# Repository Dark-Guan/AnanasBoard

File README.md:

# AnanasBoard
AnanasBoard is Designed for Stepper Closeloop Control.

<br />本作品采用<a rel="license" href="http://creativecommons.org/licenses/by/4.0/">知识共享署名 4.0 国际许可协议</a>进行许可。

如果你认为我做的这些对你来说是有价值的, 并鼓励我进行更多开源和免费的开发. 那你可以资助我, 就算是一杯咖啡...

If you find my work useful and you want to encourage the development of more free resources, you can do it by donating...

##feature

1. AMS5600 and Quadrature Encoder Supported  
2. Intelligent Tuning of the Motor Current  
3. Up to 30Khz Pulse Input Supported  
4. Up to 60Khz Stepper Driver PWM with Trapezoid Acceleration  
5. Internal PID Speed Controller  

##driver
1. A4988 and Drv8825 supported.
2. PWM DA function supported.With the  Tale:
    *PWM frequence needs to be up to 10Khz*

| IC| divider resistance | Capacitance | 5V| 3.3V
| ---------------- | ---------------- | ---------------- | ---------------- | ---------------- 
| A4988 | 10KOhm | 0.1uf | 4.7KOhm | 10KOhm
| drv8825 | 10KOhm | 0.1uf | 2.7KOhm | 3.3KOhm

circuit: voltage division circuit with a Capacitance(0.1uf)  
More Info : _[A4988](http://www.allegromicro.com/~/media/Files/Datasheets/A4988-Datasheet.ashx?la=zh-CN) and [Drv8825](http://www.ti.com/lit/ds/symlink/drv8825.pdf)datasheet_.  

# Eagle

Eagle 7.2 Used

# SoftWare
https://git.oschina.net/GaryPillow/Ananas
## back up
https://github.com/Dark-Guan/Ananas

https://github.com/Dark-Guan/Ananas/tree/master/binary

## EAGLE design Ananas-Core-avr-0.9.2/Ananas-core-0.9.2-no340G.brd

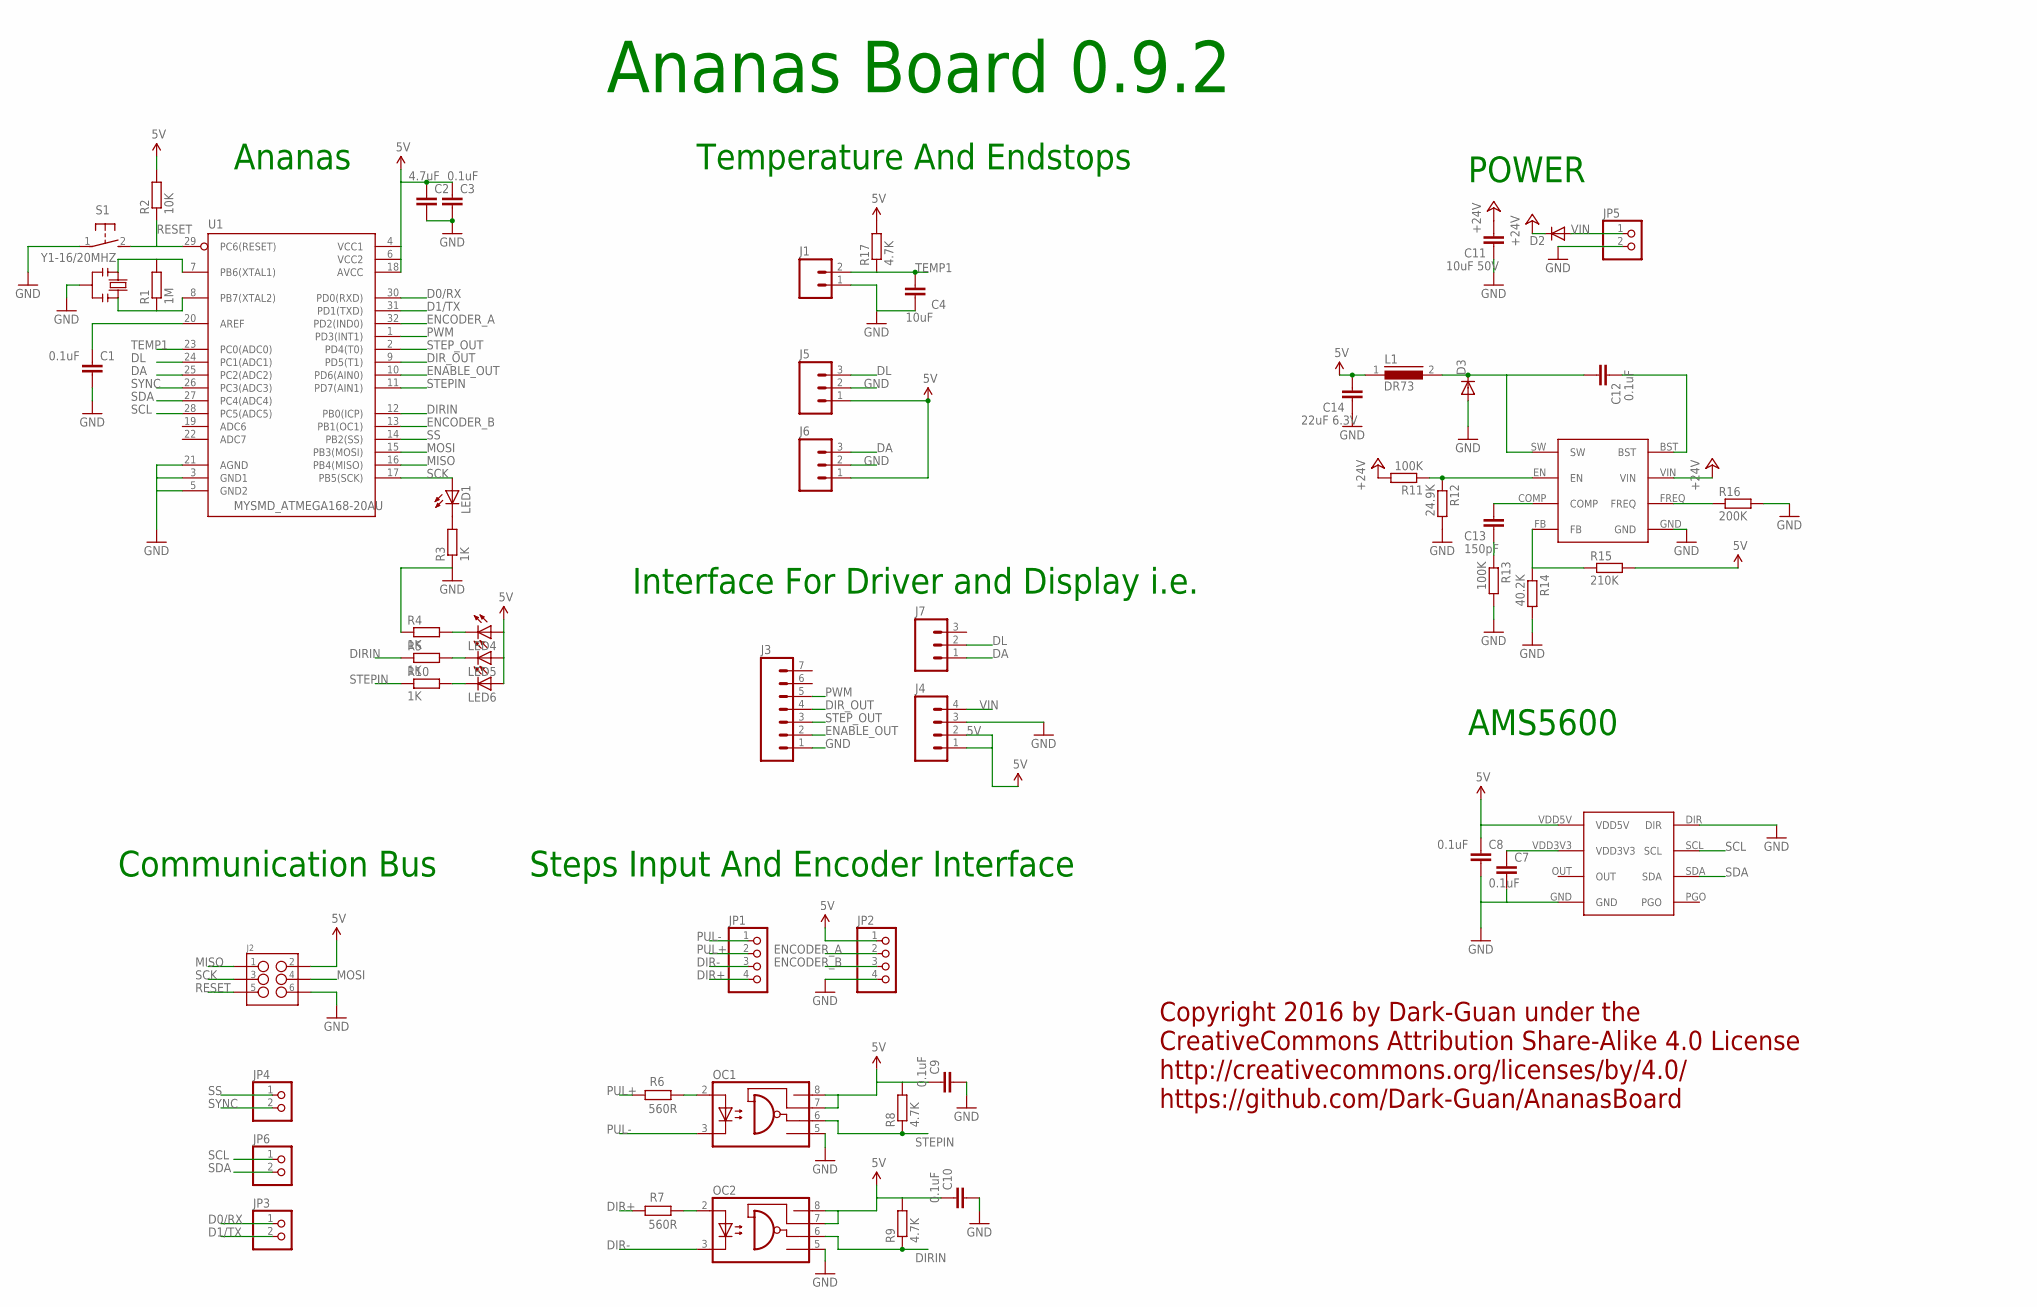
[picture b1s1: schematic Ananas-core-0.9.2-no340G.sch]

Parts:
C1, C3, C7, C8, C9, C10, C12: 0.1uF; C0603K
C2: 4.7uF; C0603K
C4: 10uF; C0603K
C11: 10uF 50V; C0805
C13: 150pF; C0603K
C14: 22uF 6.3V; C0805
D2, D3: DIODE_DIODE-SMB; DIODE_SMB
J1: M02PTH; 1X02
J2: M03X2NO_SILK; 2X3-NS
J3: M07; 1X07
J4: M04PTH; 1X04
J5, J6, J7: M03PTH; 1X03
JP1, JP2: PINHD-1X4/OCT; 1X04/OCT
JP3, JP4, JP5, JP6: PINHD-1X2/OCT; 1X02/OCT
L1: DR73
LED1, LED4, LED5, LED6: LEDCHIPLED_0603; CHIPLED_0603
MP1854: MP1584
OC1, OC2: OPTOCOUPLER_(2)_HCPL0600; OPTOCOUPLER_(2)_SOIC08
R1: 1M; R0603
R2: 10K; R0603
R3, R4, R5, R10: 1K; R0603
R6, R7: 560R; R0603
R8, R9, R17: 4.7K; R0603
R11, R13: 100K; R0603
R12: 24.9K; R0603
R14: 40.2K; R0603
R15: 210K; R0603
R16: 200K; R0603
S1: 31-XX; B3F-31XX
U1: MYSMD_ATMEGA168-20AU; MYSMD_QFP032
U$1: ARDUINO_AS5600
Y1-16/20MHZ: MYSMD2_RESONATORMU; MYSMD2_RESONATOR

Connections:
5V: C2.1, C3.1, C8.1, C9.1, C10.1, C14.2, J2.2, J4.1, J4.2, J5.1, J6.1, JP2.1, L1.1, LED4.A, LED5.A, LED6.A, OC1.7 (VE), OC1.8 (VCC), OC2.7 (VE), OC2.8 (VCC), R2.2, R8.2, R9.2, R15.2, R17.2, U1.4 (VCC1), U1.6 (VCC2), U1.18 (AVCC), U$1.VDD5V
+24V: C11.2, D2.C, MP1854.VIN, R11.2
D0/RX: JP3.1, U1.30 (PD0(RXD))
D1/TX: JP3.2, U1.31 (PD1(TXD))
DA: J6.3, J7.1, U1.25 (PC2(ADC2))
DIR+: JP1.4, R7.2
DIR-: JP1.3, OC2.3 (C)
DIRIN: OC2.6 (VO), R5.1, R9.1, U1.12 (PB0(ICP))
DIR_OUT: J3.4, U1.9 (PD5(T1))
DL: J5.3, J7.2, U1.24 (PC1(ADC1))
ENABLE_OUT: J3.2, U1.10 (PD6(AIN0))
ENCODER_A: JP2.2, U1.32 (PD2(IND0))
ENCODER_B: JP2.3, U1.13 (PB1(OC1))
GND: C1.2, C2.2, C3.2, C4.1, C7.2, C8.2, C9.2, C10.2, C11.1, C14.1, D3.A, J1.1, J2.6, J3.1, J4.3, J5.2, J6.2, JP2.4, JP5.2, MP1854.GND, OC1.5 (GND), OC2.5 (GND), R3.1, R4.1, R12.2, R13.2, R14.2, R16.2, S1.1, U1.3 (GND1), U1.5 (GND2), U1.21 (AGND), U$1.DIR, U$1.GND, Y1-16/20MHZ.2
MISO: J2.1, U1.16 (PB4(MISO))
MOSI: J2.4, U1.15 (PB3(MOSI))
unnamed: R1.2, U1.7 (PB6(XTAL1)), Y1-16/20MHZ.1
unnamed: R1.1, U1.8 (PB7(XTAL2)), Y1-16/20MHZ.3
unnamed: C1.1, U1.20 (AREF)
unnamed: OC1.2 (A), R6.1
unnamed: LED1.C, R3.2
unnamed: OC2.2 (A), R7.1
unnamed: C13.1, R13.1
unnamed: C7.1, U$1.VDD3V3
unnamed: MP1854.FREQ, R16.1
unnamed: C12.1, MP1854.BST
unnamed: C12.2, D3.C, L1.2, MP1854.SW
unnamed: MP1854.EN, R11.1, R12.1
unnamed: C13.2, MP1854.COMP
unnamed: MP1854.FB, R14.1, R15.1
unnamed: LED4.C, R4.2
unnamed: LED5.C, R5.2
unnamed: LED6.C, R10.2
PUL+: JP1.2, R6.2
PUL-: JP1.1, OC1.3 (C)
PWM: J3.5, U1.1 (PD3(INT1))
RESET: J2.5, R2.1, S1.2 (S), U1.29 (PC6(RESET))
SCK: J2.3, LED1.A, U1.17 (PB5(SCK))
SCL: JP6.1, U1.28 (PC5(ADC5)), U$1.SCL
SDA: JP6.2, U1.27 (PC4(ADC4)), U$1.SDA
SS: JP4.1, U1.14 (PB2(SS))
STEPIN: OC1.6 (VO), R8.1, R10.1, U1.11 (PD7(AIN1))
STEP_OUT: J3.3, U1.2 (PD4(T0))
SYNC: JP4.2, U1.26 (PC3(ADC3))
TEMP1: C4.2, J1.2, R17.1, U1.23 (PC0(ADC0))
VIN: D2.A, J4.4, JP5.1

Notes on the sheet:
Communication Bus
Steps Input And Encoder Interface
AMS5600
Interface For Driver and Display i.e.
Temperature And Endstops
POWER
Copyright 2016 by Dark-Guan under the CreativeCommons Attribution Share-Alike 4.0 License http://creativecommons.org/licenses/by/4.0/ https://github.com/Dark-Guan/AnanasBoard
Ananas Board 0.9.2
Ananas

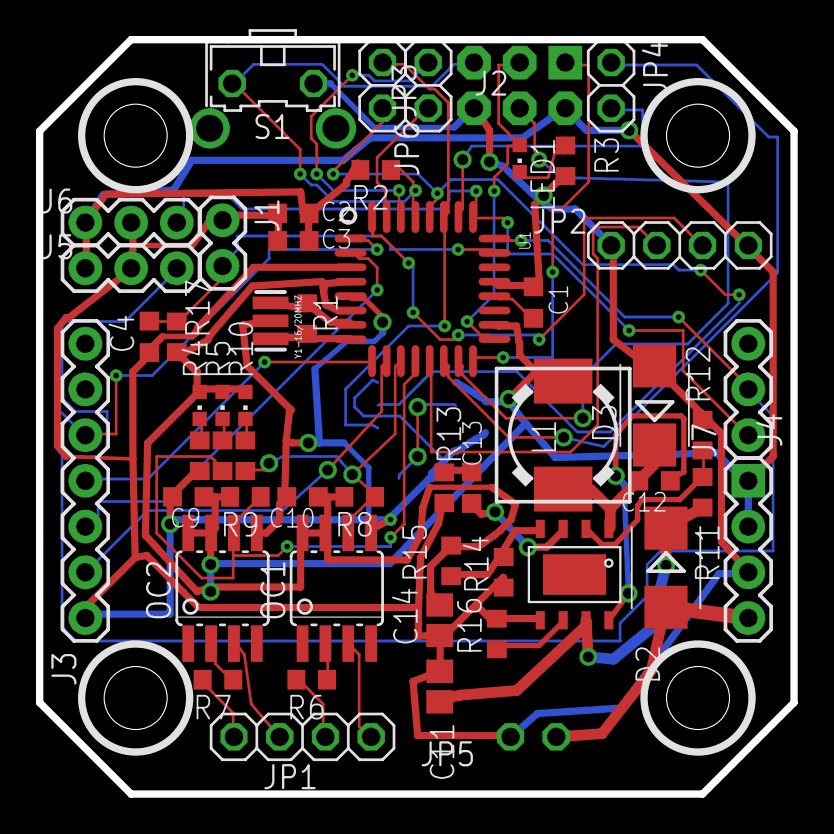
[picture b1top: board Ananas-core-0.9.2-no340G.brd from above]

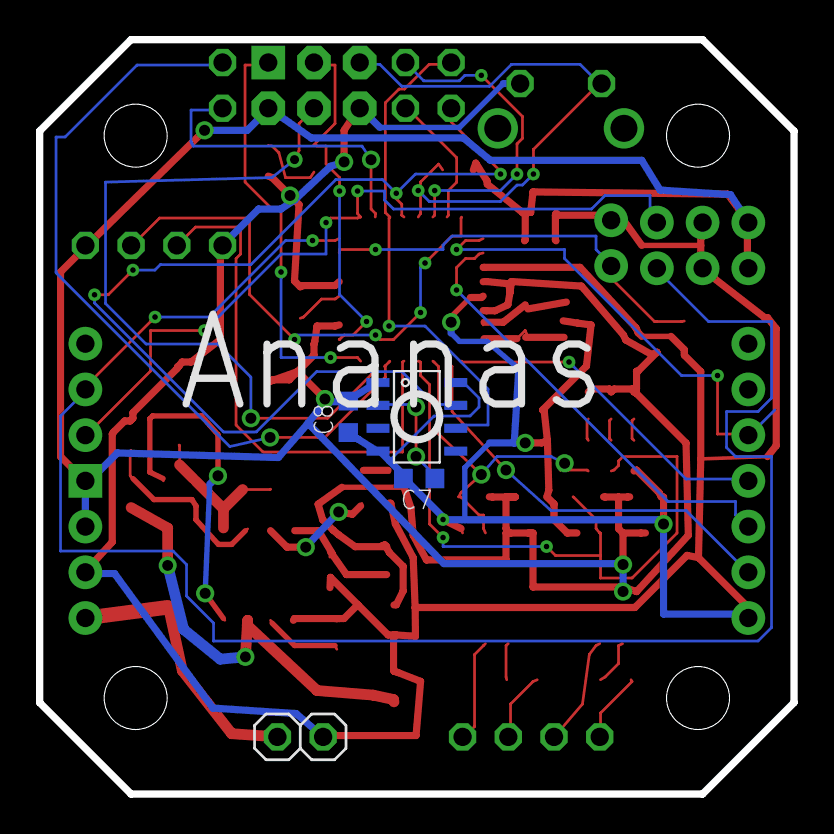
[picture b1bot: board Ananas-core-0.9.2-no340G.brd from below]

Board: 2 copper layers, 41.9 x 41.9 mm, 56 parts (4 on the bottom side), 46 nets.

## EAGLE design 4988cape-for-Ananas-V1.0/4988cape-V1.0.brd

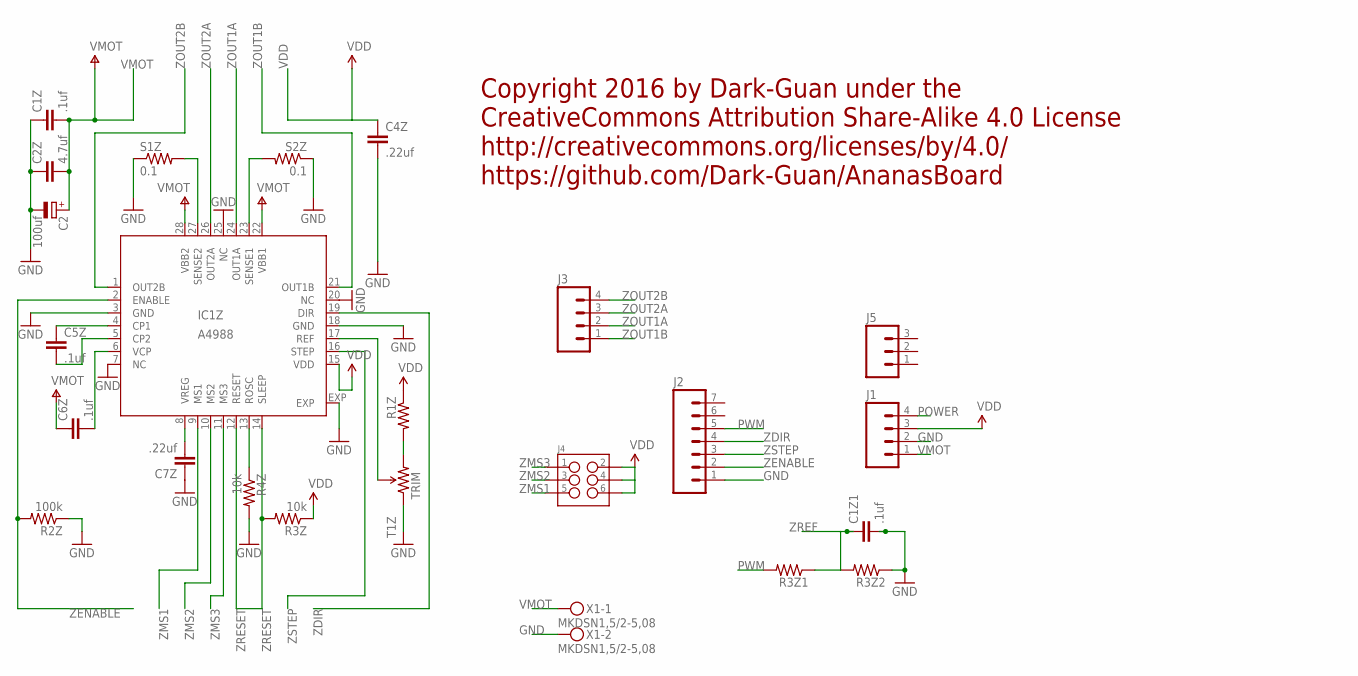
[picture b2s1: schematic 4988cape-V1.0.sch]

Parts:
C1Z, C1Z1, C5Z, C6Z: .1uf; 0402-CAP
C2: 100uf; 153CLV-0605
C2Z: 4.7uf; 0402-CAP
C4Z, C7Z: .22uf; 0402-CAP
IC1Z: A4988; QFN28ET
J1, J3: M04PTH; 1X04
J2: M07; 1X07
J4: M03X2NO_SILK; 2X3-NS
J5: M03PTH; 1X03
R1Z, R3Z1, R3Z2: RESISTOR0402-RES; 0402-RES
R2Z: 100k; 0402-RES
R3Z, R4Z: 10k; 0402-RES
S1Z, S2Z: 0.1; 0805
T1Z: TRIM; TRIMPOT-3MM
X1: MKDSN1,5/2-5,08

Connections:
GND: C1Z.1, C1Z1.2, C2.-, C2Z.1, C4Z.2, C7Z.1, IC1Z.3 (GND), IC1Z.7 (NC), IC1Z.18 (GND), IC1Z.20 (NC), IC1Z.25 (NC), IC1Z.EXP, J1.2, J2.1, R2Z.1, R3Z2.1, R4Z.2, S1Z.1, S2Z.1, T1Z.1 (CCW), X1.2
POWER: J1.4
PWM: J2.5, R3Z1.2
VDD: C4Z.1, IC1Z.15 (VDD), J1.3, J4.2, J4.4, J4.6, R1Z.1, R3Z.1
VMOT: C1Z.2, C2.+, C2Z.2, C6Z.1, IC1Z.22 (VBB1), IC1Z.28 (VBB2), J1.1, X1.1
ZCP1: C5Z.1, IC1Z.4 (CP1)
ZCP2: C5Z.2, IC1Z.5 (CP2)
ZDIR: IC1Z.19 (DIR), J2.4
ZENABLE: IC1Z.2 (ENABLE), J2.2, R2Z.2
ZMS1: IC1Z.9 (MS1), J4.5
ZMS2: IC1Z.10 (MS2), J4.3
ZMS3: IC1Z.11 (MS3), J4.1
ZOUT1A: IC1Z.24 (OUT1A), J3.2
ZOUT1B: IC1Z.21 (OUT1B), J3.1
ZOUT2A: IC1Z.26 (OUT2A), J3.3
ZOUT2B: IC1Z.1 (OUT2B), J3.4
ZREF: C1Z1.1, IC1Z.17 (REF), R3Z1.1, R3Z2.2, T1Z.2 (WIPER)
ZREF2: R1Z.2, T1Z.3 (CW)
ZRESET: IC1Z.12 (RESET), IC1Z.14 (SLEEP), R3Z.2
ZROSC: IC1Z.13 (ROSC), R4Z.1
ZSENSE1: IC1Z.23 (SENSE1), S2Z.2
ZSENSE2: IC1Z.27 (SENSE2), S1Z.2
ZSTEP: IC1Z.16 (STEP), J2.3
ZVCP: C6Z.2, IC1Z.6 (VCP)
ZVREG: C7Z.2, IC1Z.8 (VREG)

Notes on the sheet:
Copyright 2016 by Dark-Guan under the CreativeCommons Attribution Share-Alike 4.0 License http://creativecommons.org/licenses/by/4.0/ https://github.com/Dark-Guan/AnanasBoard

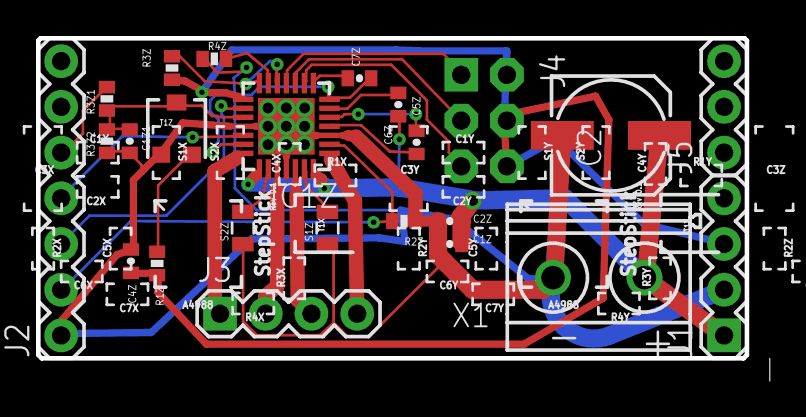
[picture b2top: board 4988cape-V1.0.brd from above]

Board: 2 copper layers, 40.5 x 18.9 mm, 24 parts (0 on the bottom side), 24 nets.

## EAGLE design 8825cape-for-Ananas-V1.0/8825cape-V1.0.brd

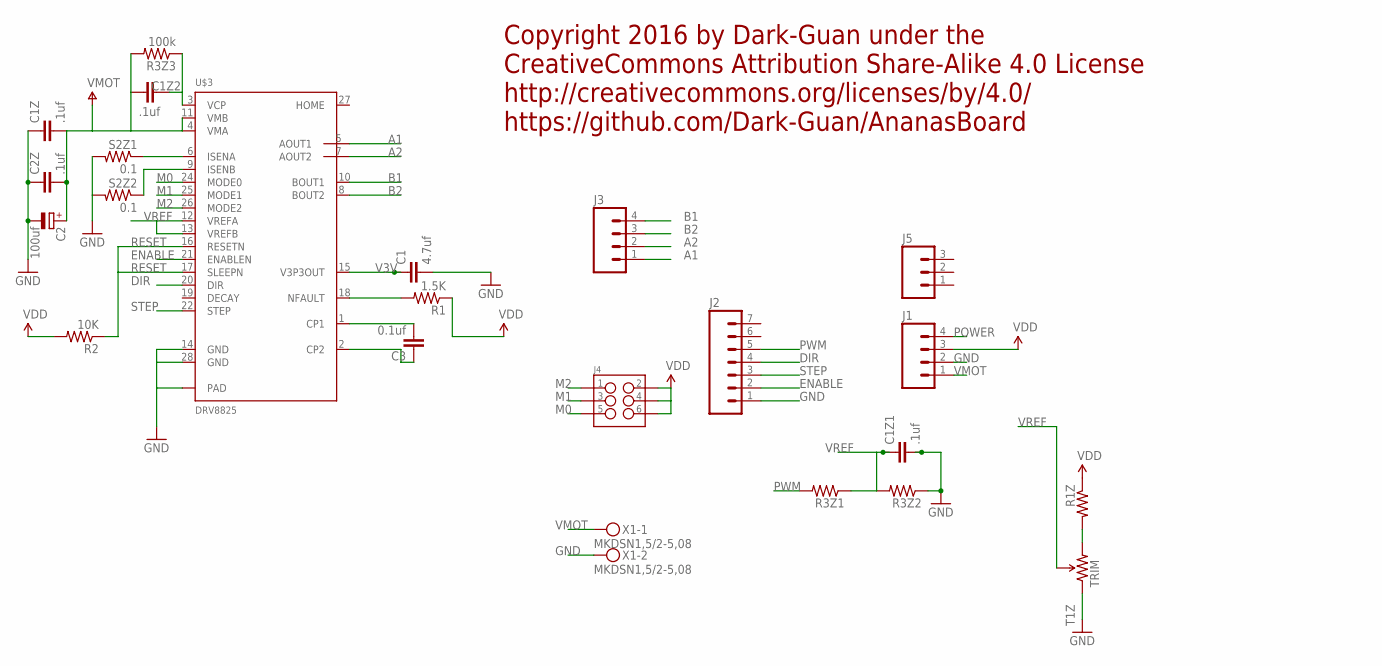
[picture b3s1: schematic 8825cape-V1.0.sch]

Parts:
C1: 4.7uf; 0402-CAP
C1Z, C1Z1, C1Z2, C2Z: .1uf; 0402-CAP
C2: 100uf; 153CLV-0605
C3: 0.1uf; 0402-CAP
J1, J3: M04PTH; 1X04
J2: M07; 1X07
J4: M03X2NO_SILK; 2X3-NS
J5: M03PTH; 1X03
R1: 1.5K; 0402-RES
R1Z, R3Z1, R3Z2: RESISTOR0402-RES; 0402-RES
R2: 10K; 0402-RES
R3Z3: 100k; 0402-RES
S2Z1, S2Z2: 0.1; 0805
T1Z: TRIM; TRIMPOT-3MM
U$3: DRV8825; HTSSOP28
X1: MKDSN1,5/2-5,08

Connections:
A1: J3.1, U$3.5 (AOUT1)
A2: J3.2, U$3.7 (AOUT2)
B1: J3.4, U$3.10 (BOUT1)
B2: J3.3, U$3.8 (BOUT2)
DIR: J2.4, U$3.20 (DIR)
ENABLE: J2.2, U$3.21 (ENABLEN)
GND: C1.2, C1Z.1, C1Z1.2, C2.-, C2Z.1, J1.2, J2.1, R3Z2.1, S2Z1.2, S2Z2.2, T1Z.1 (CCW), U$3.14 (GND), U$3.28 (GND), U$3.GND@10 (PAD), U$3.GND@11 (PAD), U$3.GND@12 (PAD), U$3.GND@13 (PAD), U$3.GND@14 (PAD), U$3.GND@15 (PAD), U$3.GND@16 (PAD), U$3.GND@17 (PAD), U$3.GND@18 (PAD), U$3.GND@19 (PAD), U$3.GND@20 (PAD), U$3.GND@21 (PAD), U$3.GND@22 (PAD), U$3.GND@23 (PAD), U$3.GND@24 (PAD), U$3.GND@25 (PAD), U$3.GND@26 (PAD), U$3.GND@27 (PAD), U$3.GND@28 (PAD), U$3.GND@29 (PAD), U$3.GND@30 (PAD), U$3.GND@PAD (PAD), X1.2
M0: J4.5, U$3.24 (MODE0)
M1: J4.3, U$3.25 (MODE1)
M2: J4.1, U$3.26 (MODE2)
unnamed: S2Z1.1, U$3.6 (ISENA)
unnamed: C1Z2.1, R3Z3.1, U$3.3 (VCP)
unnamed: C3.2, U$3.1 (CP1)
unnamed: S2Z2.1, U$3.9 (ISENB)
unnamed: C3.1, U$3.2 (CP2)
unnamed: R1.2, U$3.18 (NFAULT)
POWER: J1.4
PWM: J2.5, R3Z1.2
RESET: R2.1, U$3.16 (RESETN), U$3.17 (SLEEPN)
STEP: J2.3, U$3.22 (STEP)
V3V: C1.1, U$3.15 (V3P3OUT)
VDD: J1.3, J4.2, J4.4, J4.6, R1.1, R1Z.1, R2.2
VMOT: C1Z.2, C1Z2.2, C2.+, C2Z.2, J1.1, R3Z3.2, U$3.4 (VMA), U$3.11 (VMB), X1.1
VREF: C1Z1.1, R3Z1.1, R3Z2.2, T1Z.2 (WIPER), U$3.12 (VREFA), U$3.13 (VREFB)
ZREF2: R1Z.2, T1Z.3 (CW)

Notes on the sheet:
Copyright 2016 by Dark-Guan under the CreativeCommons Attribution Share-Alike 4.0 License http://creativecommons.org/licenses/by/4.0/ https://github.com/Dark-Guan/AnanasBoard

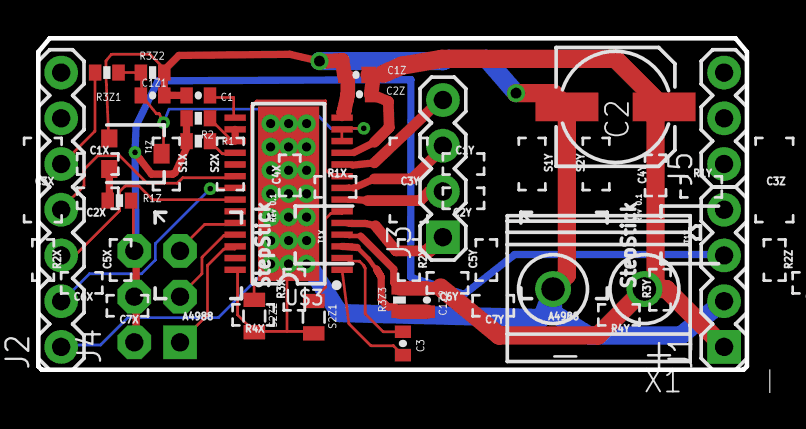
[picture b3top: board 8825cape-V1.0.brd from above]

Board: 2 copper layers, 40.5 x 19.6 mm, 23 parts (0 on the bottom side), 24 nets.

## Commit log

2016-06-05 master
2016-06-05 alipay
2016-06-07 fix the endstop
2016-06-22 fix readme
2016-07-03 fix a bug of 4988 cape
2017-06-08 update lisence
2017-06-11 update license

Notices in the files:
README.md:
CC BY 4.0
parts and their libraries:
SparkFun-Connectors: Licensing: Creative Commons ShareAlike 4.0 International - https://creativecommons.org/licenses/by-sa/4.0
